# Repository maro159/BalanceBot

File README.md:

# BalanceBot

RPi Pico based self balancing robot developed as academic project on AGH UST

**NOTE:** This project is still WIP (Work In Progress)

## Overview
A goal was to create two-wheel robot with ability to self-balance. 

|  |  |
|-|-|

### Hardware
- 2S LiIon/LiPo battery pack
- custom PCB
- RPi Pico (dual core ARM Cortex M0+)
- DRV8833 H-Bridge (much more efficient than popular L293) 
- 2x DFRobot SJ01 120:1 DC Motor with magnetic encoder
- MPU-6050 6-axis IMU (accelerometer + gyroscope)
- 2x HC04 ultrasonic distance sensor
- SSD1306 OLED display + EC11 rotary encoder 

### Software
Code was written in C language using *Raspberry Pi Pico SDK*.

Self-stabilization algorithm is based on measuring vehicle's tilt angle using accelerometer and gyroscope measurements. The angle is calculated using *complementary filter*. Idea of the filter is to estimate angle avoiding errors from gyroscope low frequency components and accelerometer high frequency components.

Next stage of controller consists of 3-level cascade of PID controllers:

|name|set point|input|output|description|
|-|-|-|-|-|
|pid_speed|target_robot_speed|current_robot_speed|target_angle|calculate angle needed to reach target_robot_speed|
|pid_imu|target_angle|current_angle|target_motor_speed|calculate motor speed needed to reach target_angle|
|pid_motor_a|target_motor_speed|current_motor_a_speed|motor_a_power|calculate power (PWM duty cycle) needed to achieve current_motor_a_speed|
|pid_motor_b|target_motor_speed|current_motor_b_speed|motor_b_power|calculate power (PWM duty cycle) needed to achieve current_motor_b_speed|

This may seem little unintuitive on first sight, but makes robot able to balance "in place" instead of drifting to either side. Such algorithm was possible to implement thanks to motor encoders. Working principle is explained pretty well [on Husarion blog](https://medium.com/husarion-blog/fresh-look-at-self-balancing-robot-algorithm-d50d41711d58), where we got the idea from. Thanks a lot for publishing it!

PID coefficients can be set via OLED GUI, which can be navigated using rotary encoder. Big thanks to David Schramm for the [pico ssd1306 library](https://github.com/daschr/pico-ssd1306)

All of above runs on a single core. There is a plan to use second core for wireless communication and further expand abilities of the robot 

### PC App
There is a [python script](PC/main.py) included, which implements plotting data received on serial port. It is simple and unoptimized, but was really helpful during debugging and tuning of complementary filter and PID controllers.
 
## Further development
- design new frame to lower center of mass -> lower moment of inertia
- replace heavy 18650 LiIon battery pack with light LiPo 
- improve IMU measurements by using MPU-6050's interrupt
- fine-tune PIDs
- implement driving and remote control
- implement obstacle detection using ultrasonic sensors

## Attribution
- *slightly modified* [SSD1306 library by David Schramm](https://github.com/daschr/pico-ssd1306)
- idea of PID cascade from [husarion/self-balancing-telepresence-robot](https://github.com/husarion/self-balancing-telepresence-robot) and [Husarion Medium blog](https://medium.com/husarion-blog/fresh-look-at-self-balancing-robot-algorithm-d50d41711d58)

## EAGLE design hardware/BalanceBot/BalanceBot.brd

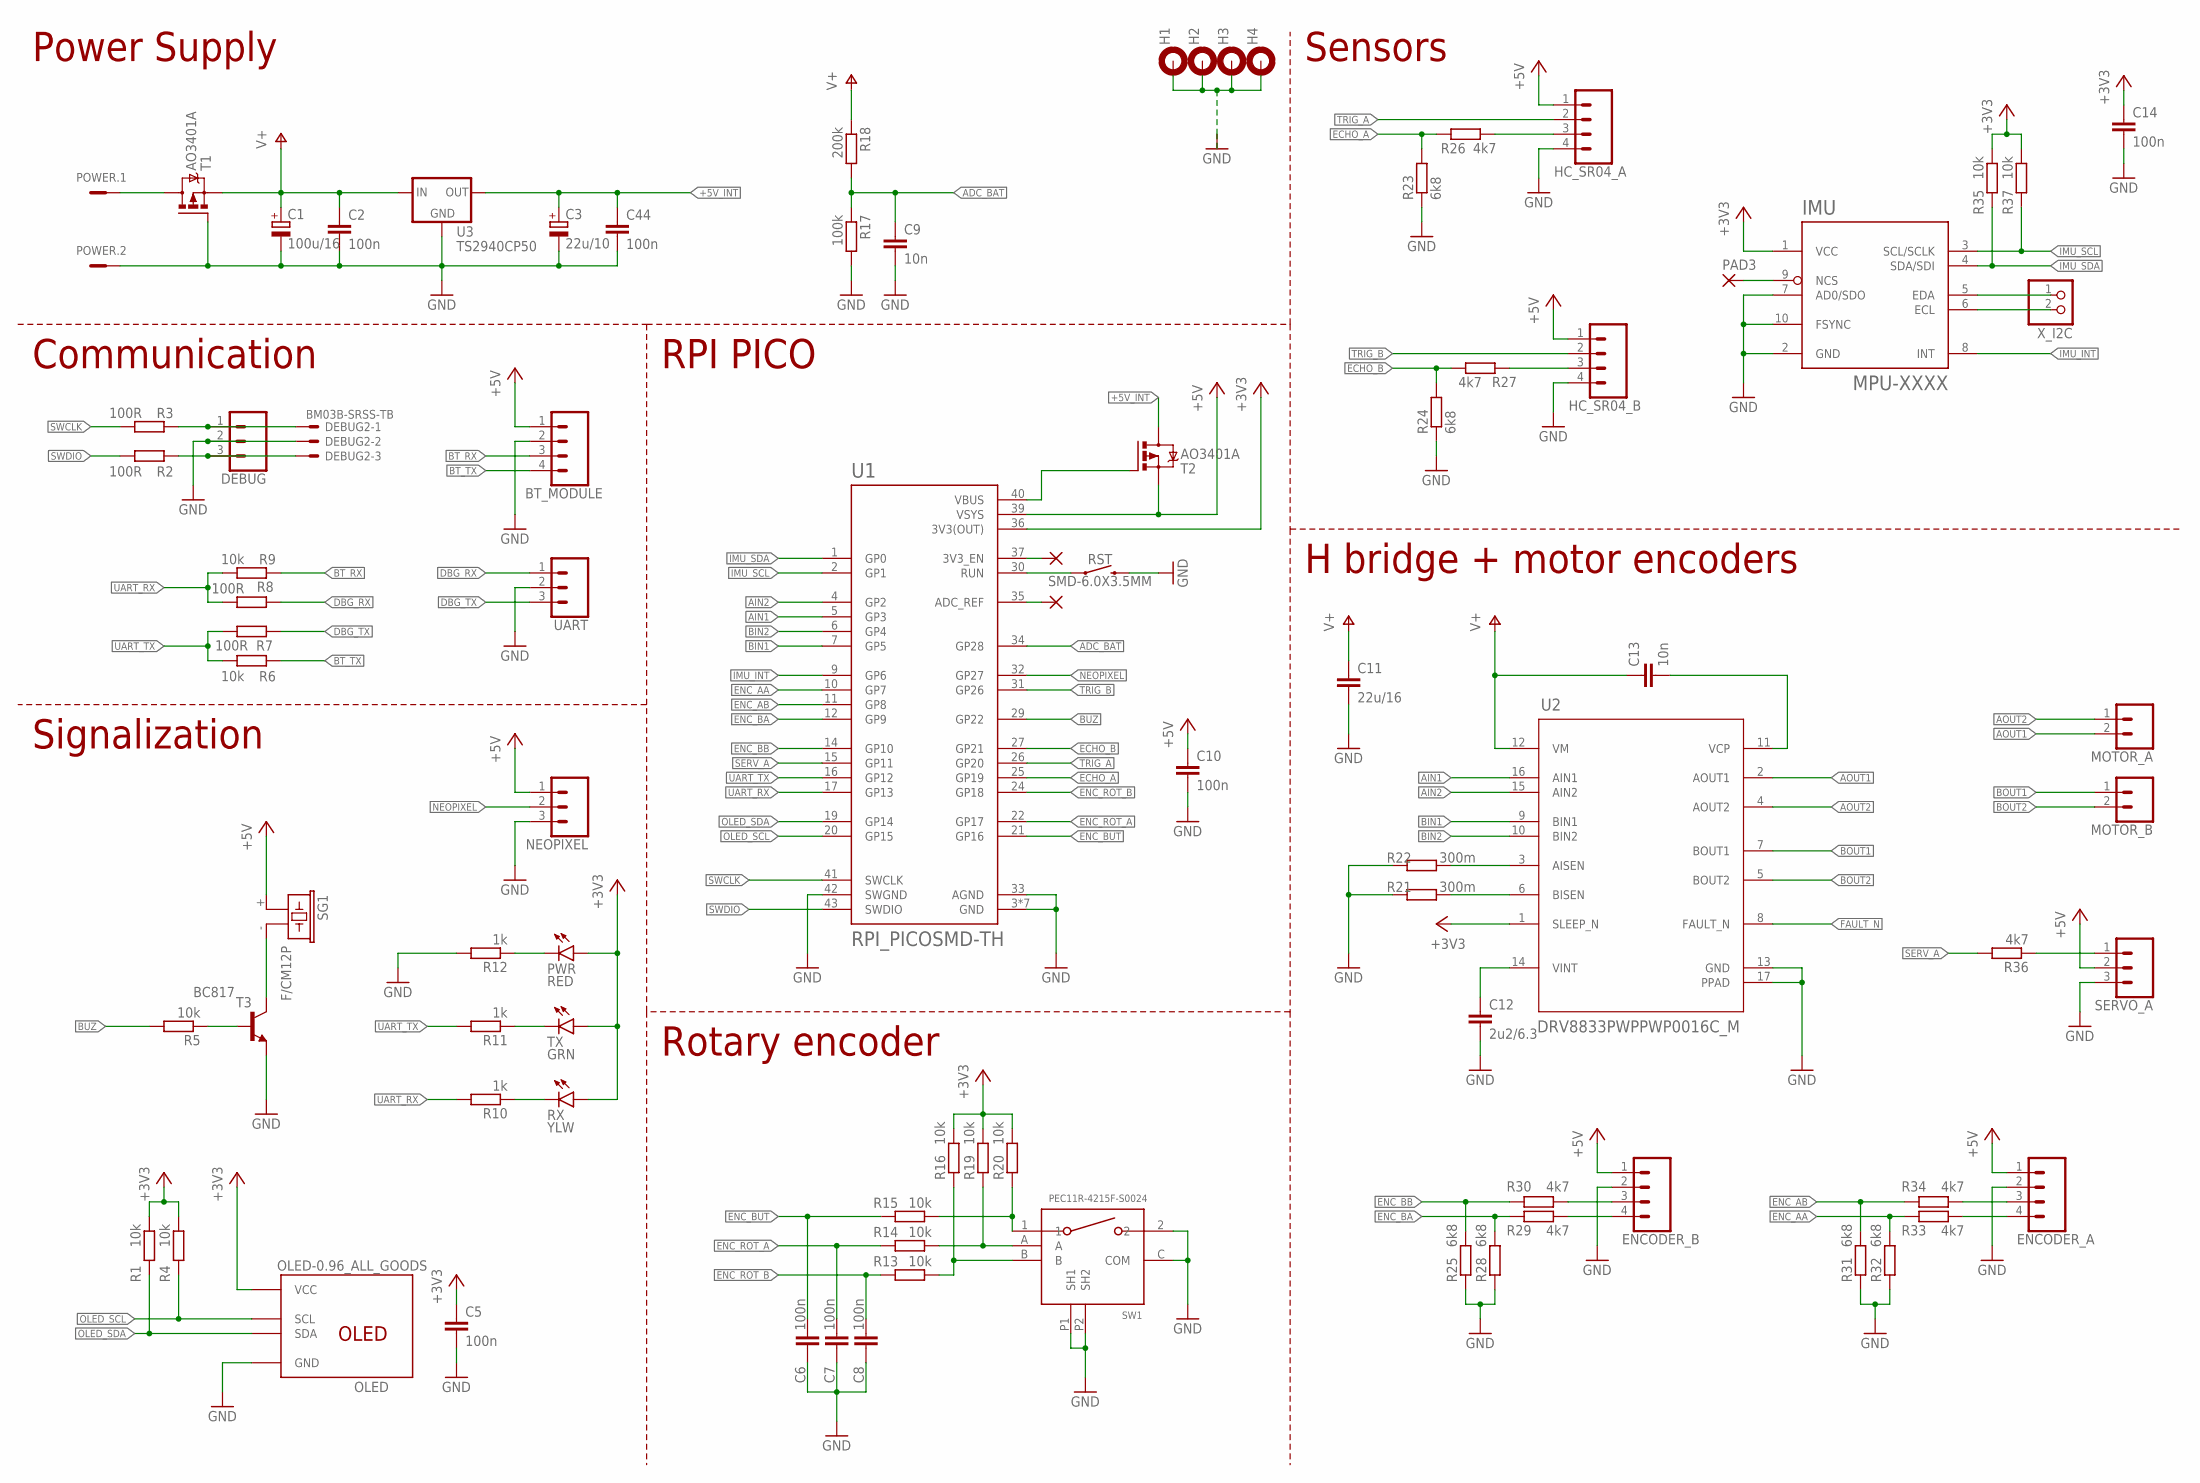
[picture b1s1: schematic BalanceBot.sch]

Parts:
BT_MODULE: JST-XH-04-PIN-LONG-PAD; JST-XH-04-PACKAGE-LONG-PAD
C1: 100u/16; E2-5
C2, C5, C6, C7, C8, C10, C14, C44: 100n; C0805
C3: 22u/10; SMC_B
C9, C13: 10n; C0805
C11: 22u/16; C0805
C12: 2u2/6.3; C0805
DEBUG: JST-XH-03-PIN-LONG-PAD; JST-XH-03-PACKAGE-LONG-PAD
DEBUG2: BM03B-SRSS-TB
ENCODER_A: JST-XH-04-PIN-LONG-PAD; JST-XH-04-PACKAGE-LONG-PAD
ENCODER_B: JST-XH-04-PIN-LONG-PAD; JST-XH-04-PACKAGE-LONG-PAD
H1, H2, H3, H4: MOUNT-PAD-ROUND3.2; 3,2-PAD
HC_SR04_A, HC_SR04_B: JST-XH-04-PIN-LONG-PAD; JST-XH-04-PACKAGE-LONG-PAD
IMU: MPU-XXXX; MPUXXXX
MOTOR_A: JST-XH-02-PIN-LONG-PAD; JST-XH-02-PACKAGE-LONG-PAD
MOTOR_B: JST-XH-02-PIN-LONG-PAD; JST-XH-02-PACKAGE-LONG-PAD
NEOPIXEL: JST-XH-03-PIN-LONG-PAD; JST-XH-03-PACKAGE-LONG-PAD
OLED: OLED-0.96_ALL_GOODS; ALL_GOODS
PAD1, PAD2, PAD3: WIREPADSMD1,27-254; SMD1,27-2,54
POWER: MCV2
PWR: RED; CHIP-LED0805
R1, R4, R5, R6, R9, R13, R14, R15, R16, R19, R20, R35, R37: 10k; R0805
R2, R3, R7, R8: 100R; R0805
R10, R11, R12: 1k; R0805
R17: 100k; R0805
R18: 200k; R0805
R21, R22: 300m; R1206
R23, R24, R25, R28, R31, R32: 6k8; R0805
R26, R27, R29, R30, R33, R34, R36: 4k7; R0805
RST: SMD-6.0X3.5MM; TACTILE_SWITCH_SMD_6.0X3.5MM
RX: YLW; CHIP-LED0805
SERVO_A: JST-XH-03-PIN-LONG-PAD; JST-XH-03-PACKAGE-LONG-PAD
SG1: F/CM12P
SW1: PEC11R-4215F-S0024
T1, T2: AO3401A; SOT23
T3: BC817; SOT23-BEC
TX: GRN; CHIP-LED0805
U1: RPI_PICOSMD-TH; PICO-PKG-TH-ONLY
U2: DRV8833PWPPWP0016C_M; PWP0016C_M
U3: TS2940CP50; DPACK
UART: JST-XH-03-PIN-LONG-PAD; JST-XH-03-PACKAGE-LONG-PAD
X_I2C: PINHD-1X2; 1X02

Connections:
3V3_EN: PAD2.1, U1.37 (3V3_EN)
+3V3: C5.1, C14.1, IMU.1 (VCC), OLED.2 (VCC), PWR.A, R1.1, R4.1, R16.1, R19.1, R20.1, R35.1, R37.1, RX.A, TX.A, U1.36 (3V3(OUT)), U2.1 (SLEEP_N)
+5V: BT_MODULE.1, C10.1, ENCODER_A.1, ENCODER_B.1, HC_SR04_A.1, HC_SR04_B.1, NEOPIXEL.1, SERVO_A.2, SG1.+ (1), T2.2 (S), U1.39 (VSYS)
+5V_INT: C3.+, C44.1, T2.3 (D), U3.3 (OUT)
ADC_BAT: C9.1, R17.1, R18.2, U1.34 (GP28)
ADC_REF: PAD1.1, U1.35 (ADC_REF)
AIN1: U1.5 (GP3), U2.16 (AIN1)
AIN2: U1.4 (GP2), U2.15 (AIN2)
AOUT1: MOTOR_A.2, U2.2 (AOUT1)
AOUT2: MOTOR_A.1, U2.4 (AOUT2)
BIN1: U1.7 (GP5), U2.9 (BIN1)
BIN2: U1.6 (GP4), U2.10 (BIN2)
BOUT1: MOTOR_B.1, U2.7 (BOUT1)
BOUT2: MOTOR_B.2, U2.5 (BOUT2)
BT_RX: BT_MODULE.3, R9.1
BT_TX: BT_MODULE.4, R6.1
BUZ: R5.2, U1.29 (GP22)
DBG_RX: R8.1, UART.1
DBG_TX: R7.1, UART.3
ECHO_A: R23.2, R26.1, U1.25 (GP19)
ECHO_B: R24.2, R27.1, U1.27 (GP21)
ECL: IMU.6 (ECL), X_I2C.2
EDA: IMU.5 (EDA), X_I2C.1
ENC_AA: R32.2, R33.1, U1.10 (GP7)
ENC_AB: R31.2, R34.2, U1.11 (GP8)
ENC_BA: R28.2, R29.1, U1.12 (GP9)
ENC_BB: R25.2, R30.2, U1.14 (GP10)
ENC_BUT: C6.1, R15.1, U1.21 (GP16)
ENC_ROT_A: C7.1, R14.1, U1.22 (GP17)
ENC_ROT_B: C8.1, R13.1, U1.24 (GP18)
FAULT_N: U2.8 (FAULT_N)
GND: BT_MODULE.2, C1.-, C2.2, C3.-, C5.2, C6.2, C7.2, C8.2, C9.2, C10.2, C11.2, C12.2, C14.2, C44.2, DEBUG.2, DEBUG2.2, ENCODER_A.2, ENCODER_B.2, H1.B3,2, H2.B3,2, H3.B3,2, H4.B3,2, HC_SR04_A.4, HC_SR04_B.4, IMU.2 (GND), IMU.7 (AD0/SDO), IMU.10 (FSYNC), NEOPIXEL.3, OLED.1 (GND), POWER.2, R12.2, R17.2, R21.1, R22.1, R23.1, R24.1, R25.1, R28.1, R31.1, R32.1, RST.2, SERVO_A.3, SW1.2, SW1.C (COM), SW1.P1 (SH1), SW1.P2 (SH2), T1.1 (G), T3.E, U1.3 (GND), U1.8 (GND), U1.13 (GND), U1.18 (GND), U1.23 (GND), U1.28 (GND), U1.33 (AGND), U1.38 (GND), U1.42 (SWGND), U2.13 (GND), U2.17 (PPAD), U3.4 (GND), UART.2
IMU_INT: IMU.8 (INT), U1.9 (GP6)
IMU_SCL: IMU.3 (SCL/SCLK), R37.2, U1.2 (GP1)
IMU_SDA: IMU.4 (SDA/SDI), R35.2, U1.1 (GP0)
unnamed: R22.2, U2.3 (AISEN)
unnamed: R21.2, U2.6 (BISEN)
unnamed: C13.2, U2.11 (VCP)
unnamed: C12.1, U2.14 (VINT)
unnamed: POWER.1, T1.3 (D)
unnamed: PWR.C, R12.1
unnamed: R11.1, TX.C
unnamed: R15.2, R20.2, SW1.1
unnamed: R5.1, T3.B
unnamed: R14.2, R19.2, SW1.A
unnamed: SG1.- (2), T3.C
unnamed: R13.2, R16.2, SW1.B
unnamed: R10.1, RX.C
unnamed: HC_SR04_A.3, R26.2
unnamed: HC_SR04_B.3, R27.2
unnamed: ENCODER_A.3, R34.1
unnamed: ENCODER_A.4, R33.2
unnamed: ENCODER_B.3, R30.1
unnamed: ENCODER_B.4, R29.2
unnamed: DEBUG.1, DEBUG2.1, R3.1
unnamed: R36.1, SERVO_A.1
unnamed: DEBUG.3, DEBUG2.3, R2.2
NCS: IMU.9 (NCS), PAD3.1
NEOPIXEL: NEOPIXEL.2, U1.32 (GP27)
OLED_SCL: OLED.3 (SCL), R4.2, U1.20 (GP15)
OLED_SDA: OLED.4 (SDA), R1.2, U1.19 (GP14)
RUN: RST.1, U1.30 (RUN)
SERV_A: R36.2, U1.15 (GP11)
SWCLK: R3.2, U1.41 (SWCLK)
SWDIO: R2.1, U1.43 (SWDIO)
TRIG_A: HC_SR04_A.2, U1.26 (GP20)
TRIG_B: HC_SR04_B.2, U1.31 (GP26)
UART_RX: R8.2, R9.2, R10.2, U1.17 (GP13)
UART_TX: R6.2, R7.2, R11.2, U1.16 (GP12)
V+: C1.+, C2.1, C11.1, C13.1, R18.1, T1.2 (S), U2.12 (VM), U3.1 (IN)
VBUS: T2.1 (G), U1.40 (VBUS)

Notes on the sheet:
RPI PICO
Power Supply
Communication
Signalization
Rotary encoder
H bridge + motor encoders
Sensors

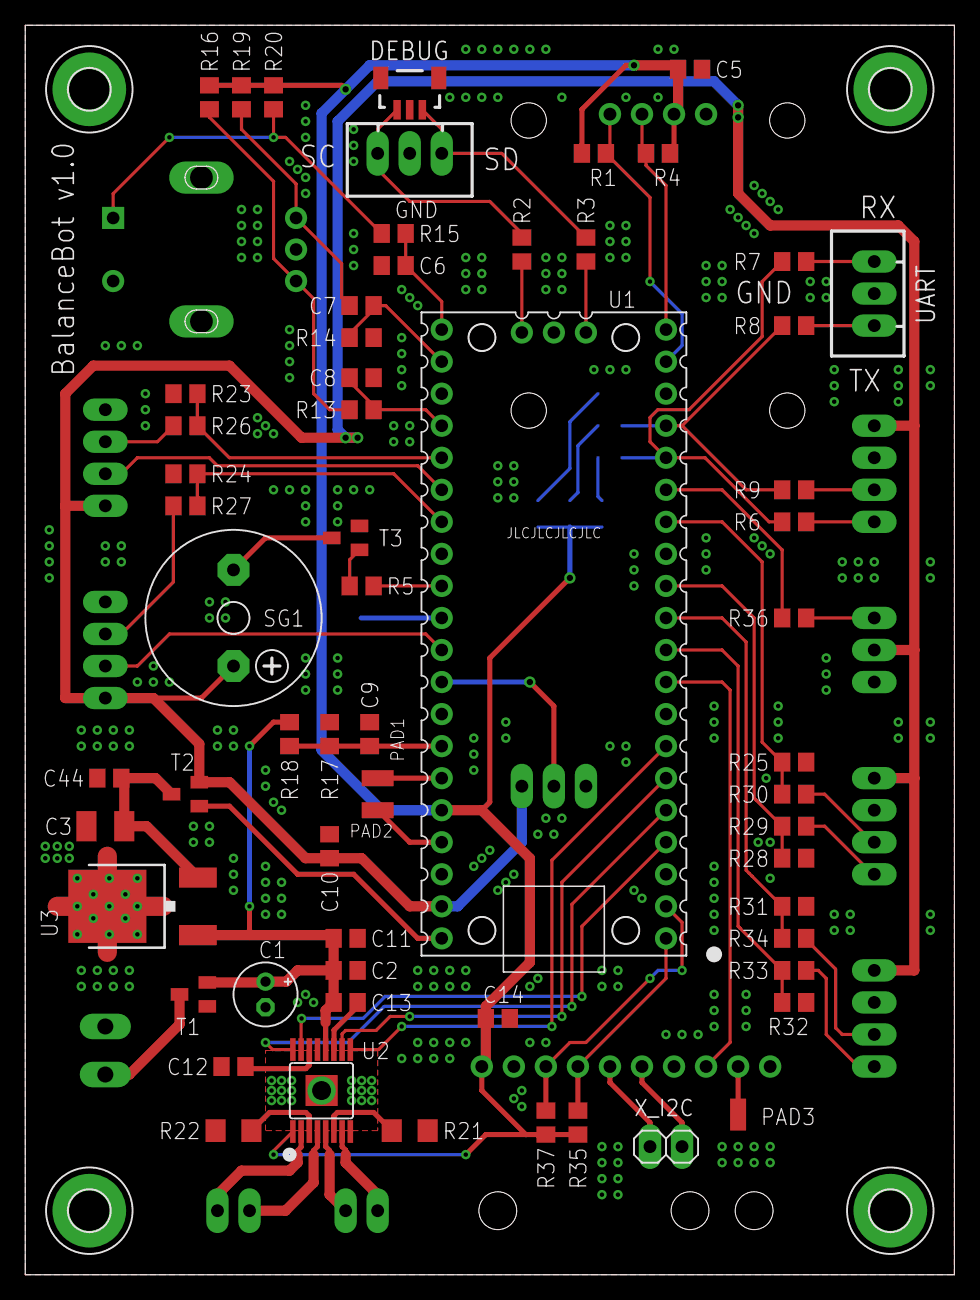
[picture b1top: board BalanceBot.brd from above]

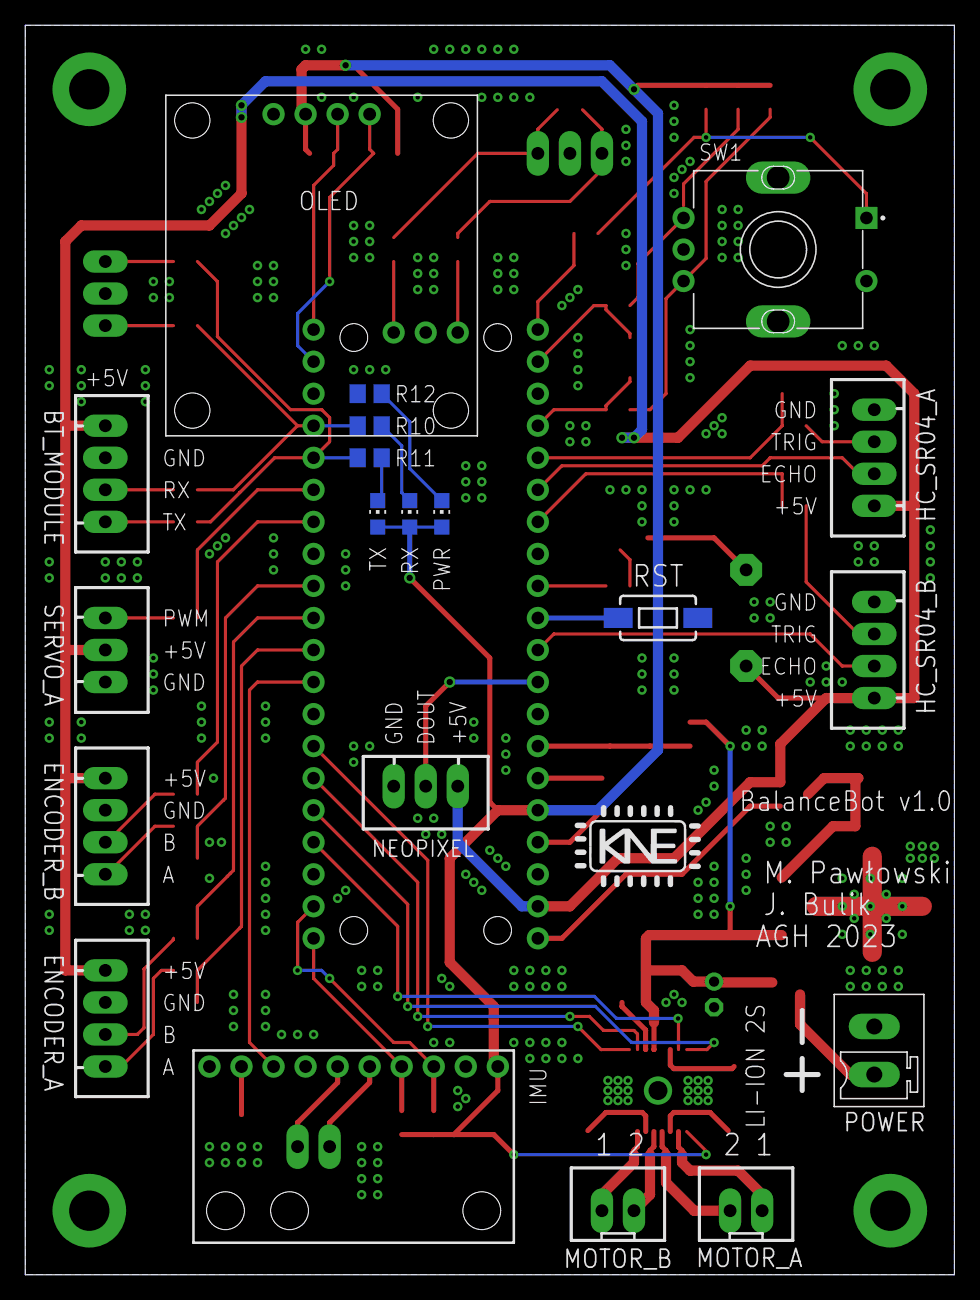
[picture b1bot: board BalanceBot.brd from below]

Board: 2 copper layers, 73.7 x 99.1 mm, 86 parts (20 on the bottom side), 70 nets.

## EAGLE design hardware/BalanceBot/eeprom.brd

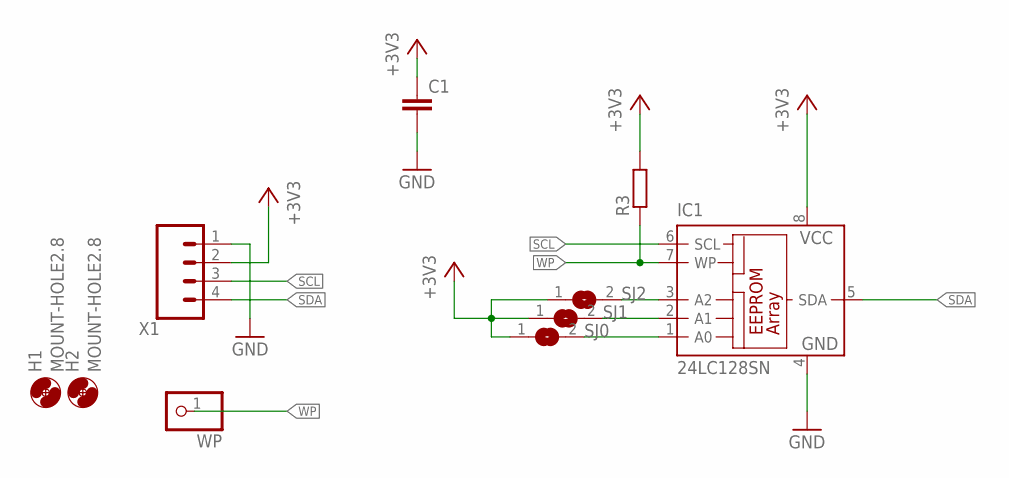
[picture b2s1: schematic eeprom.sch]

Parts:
C1: C-EUC0805; C0805
H1, H2: MOUNT-HOLE2.8; 2,8
IC1: 24LC128SN; SO-08
R3: R-EU_R0805; R0805
SJ0, SJ1, SJ2: SJ
WP: PINHD-1X1; 1X01
X1: JST-XH-04-PIN-ROUND-PAD; JST-XH-04-PACKAGE-ROUND-PAD

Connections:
+3V3: C1.1, IC1.8 (VCC), R3.2, SJ0.1, SJ1.1, SJ2.1, X1.2
GND: C1.2, IC1.4 (GND), X1.1
unnamed: IC1.3 (A2), SJ2.2
unnamed: IC1.2 (A1), SJ1.2
unnamed: IC1.1 (A0), SJ0.2
SCL: IC1.6 (SCL), X1.3
SDA: IC1.5 (SDA), X1.4
WP: IC1.7 (WP), R3.1, WP.1

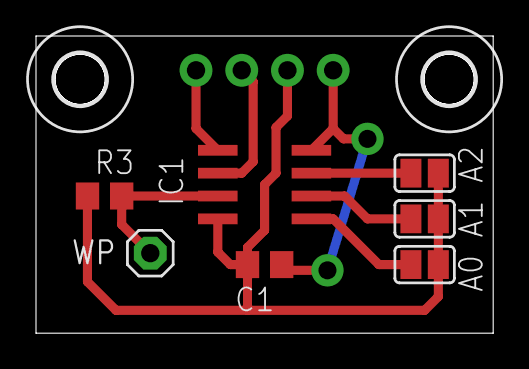
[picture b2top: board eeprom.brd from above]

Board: 2 copper layers, 25.4 x 16.5 mm, 10 parts (1 on the bottom side), 8 nets.

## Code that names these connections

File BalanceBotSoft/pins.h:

#ifndef _PINS_H_
#define _PINS_H_

// #define DEBUG_MODE

#define IMU_SDA 0
#define IMU_SCL 1
#define IMU_INT 6
#define IMU_I2C i2c0
#define IMU_BAUDRATE 400*1000

#define OLED_SDA 14
#define OLED_SCL 15
#define OLED_I2C i2c1
#define OLED_BAUDRATE 400*1000

#define BT_TX 12
#define BT_RX 13
#define BT_UART uart0
#define BT_BAUDRATE 115200

#define SERWO 11 
#define SERWO_SLICE 5
#define SERWO_CHAN PWM_CHAN_B

#define MOTOR_A1 3
#define MOTOR_A2 2
#define MOTOR_B1 5
#define MOTOR_B2 4
#define MOTOR_A_SLICE 1
#define MOTOR_A1_CHAN PWM_CHAN_B
#define MOTOR_A2_CHAN PWM_CHAN_A
#define MOTOR_B_SLICE 2
#define MOTOR_B1_CHAN PWM_CHAN_B
#define MOTOR_B2_CHAN PWM_CHAN_A

#define MOTOR_ENC_AA 7
#define MOTOR_ENC_AB 8
#define MOTOR_ENC_BA 9
#define MOTOR_ENC_BB 10

#define ENC_ROT_A 17
#define ENC_ROT_B 18
#define ENC_ROT_SW 16

#define HC04_A_TRIG 20
#define HC04_B_TRIG 26
#define HC04_A_ECHO 19
#define HC04_B_ECHO 21

#define BUZZ 22
#define NEOPX 27 // albo EEPROM_WP

#define BATTERY_LVL 28
#define BATTERY_LVL_ADC 2 // adc channel 


#endif

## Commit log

2023-06-17 Add files
2023-06-17 edit settings
2023-06-17 more settings
2023-06-17 add arm gcc kit
2023-06-17 add modified files
2023-06-17 encoder_tests
2023-06-18 cleaning
2023-06-18 multiple files example
2023-06-18 add motor support
2023-06-19 add oled files
2023-06-20 menu
2023-06-20 add acc_gyro files
2023-06-21 menu small changes
2023-06-21 menu prototype add
2023-06-22 repaired files
    change of adresses,
    mpu file deletion
2023-06-22 improve menu and encoder
2023-06-23 calculation of angles
2023-06-23 add pid support
2023-06-23 cleanup oled and menu
2023-06-23 cleanup
2023-06-23 menu and oled improvements
2023-06-23 add controler
2023-06-23 update controler
2023-06-25 modyfing controler ,motor, timer
2023-06-25 update menu
2023-06-26 fix menu
2023-06-26 link everything together
2023-06-26 add static keywords, fix timer
2023-06-27 improvement of pids and motors
2023-06-30 first test passed
2023-07-02 improve controler & encoder
2023-07-07 small fixes
    invert logo
    inverse encoder of motor B
    add pc data visualizer
2023-09-01 minor refactor
2023-09-01 refactor
    - improve menu creation
    - add static keywords where needed
    - unifcation of naming convention
2023-09-01 clean
2023-10-19 add static keyword
2023-12-05 add readme and images
2023-12-06 add pcb files
2023-12-06 fix typo in CMakeLists
2024-01-11 refactor code
    - remove global variables from imu.c/imu.h
    - rename motor motor_encoder_get to motor_encoder_fetch
    - fix pid menu entries
    - set sample time in main.c only
2024-01-11 fall detection
    stop motors when angle > 45
2024-01-14 simplify .gitignore
2024-01-15 rc prototype
2024-01-15 Update pit coef.
2024-01-15 tune pids, add filters
2024-01-15 update python scripts
2024-01-16 fight memory leaks
2024-01-18 add float suffix
2024-01-18 add memory info
2024-01-18 crazy solution
2024-01-19 optimize float
2024-01-19 Add bt turns control.
2024-01-19 Update controler.c
    quick fixes
2024-01-19 Add remote control with arduino joystick app.
2024-01-19 Quick zero angle fix.
2024-01-22 adding files to handle internal pico bluetooth
2024-01-23 Internal BT worked - 1st remote pico w working
2024-01-24 pid tune etc

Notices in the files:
parts and their libraries:
SparkFun-Switches: Licensing: Creative Commons ShareAlike 4.0 International - https://creativecommons.org/licenses/by-sa/4.0
COPYRIGHT: Copyright (C) 2023 Ultra Librarian. All rights reserved.
